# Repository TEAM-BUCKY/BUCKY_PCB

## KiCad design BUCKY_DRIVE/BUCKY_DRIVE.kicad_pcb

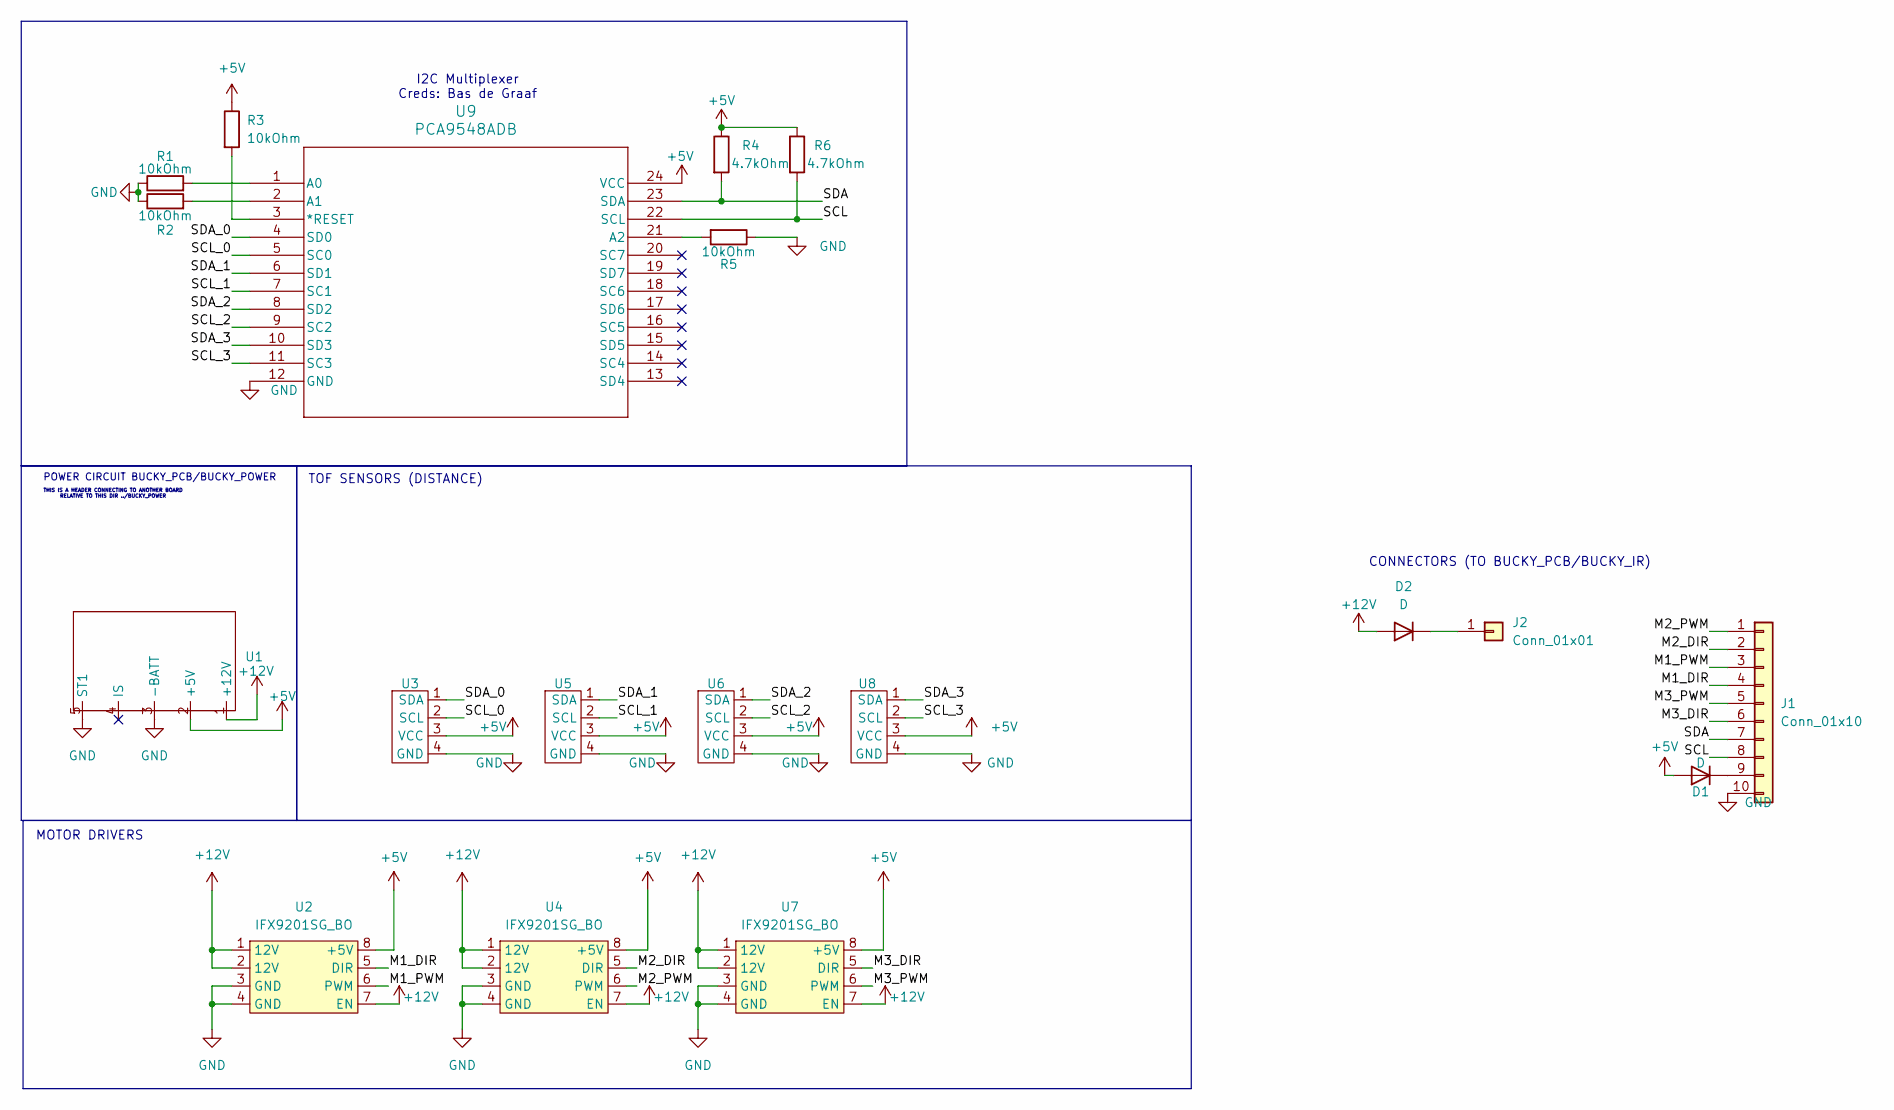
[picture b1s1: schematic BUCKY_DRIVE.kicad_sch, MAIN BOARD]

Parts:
D1: D; D_0805_2012Metric
D2: D
J1: Conn_01x10; CONN10_S10B-PH_JST
J2: Conn_01x01; PinHeader_1x01_P2.54mm_Vertical
R1, R2, R3, R5: 10kOhm; R_0805_2012Metric
R4, R6: 4.7kOhm; R_0805_2012Metric
U1: BUCKY_POWER
U2, U4, U7: IFX9201SG_BO
U3, U5, U6, U8: BUCKY_TOF
U9: PCA9548ADB; DB24

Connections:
+5V: D1.2 (A), J2.4, R3.1, R4.1, R6.1, U1.2 (+5V), U2.8 (+5V), U3.3 (VCC), U4.8 (+5V), U5.3 (VCC), U6.3 (VCC), U7.8 (+5V), U8.3 (VCC), U9.24 (VCC)
+12V: D2.2 (A), U1.1 (+12V), U2.1 (12V), U2.2 (12V), U2.7 (EN), U4.1 (12V), U4.2 (12V), U4.7 (EN), U7.1 (12V), U7.2 (12V), U7.7 (EN)
/M1_DIR: J1.4, U2.5 (DIR)
/M1_PWM: J1.3, U2.6 (PWM)
/M2_DIR: J1.2, U4.5 (DIR)
/M2_PWM: J1.1, U4.6 (PWM)
/M3_DIR: J1.6, U7.5 (DIR)
/M3_PWM: J1.5, U7.6 (PWM)
/SCL: J1.8, J2.2, R6.2, U9.22 (SCL)
/SCL_0: U3.2 (SCL), U9.5 (SC0)
/SCL_1: U5.2 (SCL), U9.7 (SC1)
/SCL_2: U6.2 (SCL), U9.9 (SC2)
/SCL_3: U8.2 (SCL), U9.11 (SC3)
/SDA: J1.7, J2.3, R4.2, U9.23 (SDA)
/SDA_0: U3.1 (SDA), U9.4 (SD0)
/SDA_1: U5.1 (SDA), U9.6 (SD1)
/SDA_2: U6.1 (SDA), U9.8 (SD2)
/SDA_3: U8.1 (SDA), U9.10 (SD3)
GND: D2.1 (K), J1.10, J2.1, R1.1, R2.1, R5.1, U1.3 (-BATT), U1.5 (ST1), U2.3 (GND), U2.4 (GND), U3.4 (GND), U4.3 (GND), U4.4 (GND), U5.4 (GND), U6.4 (GND), U7.3 (GND), U7.4 (GND), U8.4 (GND), U9.12 (GND)
unnamed: D1.1 (K), J1.9
unnamed: R3.2, U9.3 (*RESET)
unnamed: R1.2, U9.1 (A0)
unnamed: R2.2, U9.2 (A1)
unnamed: R5.2, U9.21 (A2)

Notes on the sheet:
CONNECTORS (TO BUCKY_PCB/BUCKY_IR)
TOF SENSORS (DISTANCE)
I2C Multiplexer Creds: Bas de Graaf
THIS IS A HEADER CONNECTING TO ANOTHER BOARD RELATIVE TO THIS DIR ../BUCKY_POWER
MOTOR DRIVERS
POWER CIRCUIT BUCKY_PCB/BUCKY_POWER

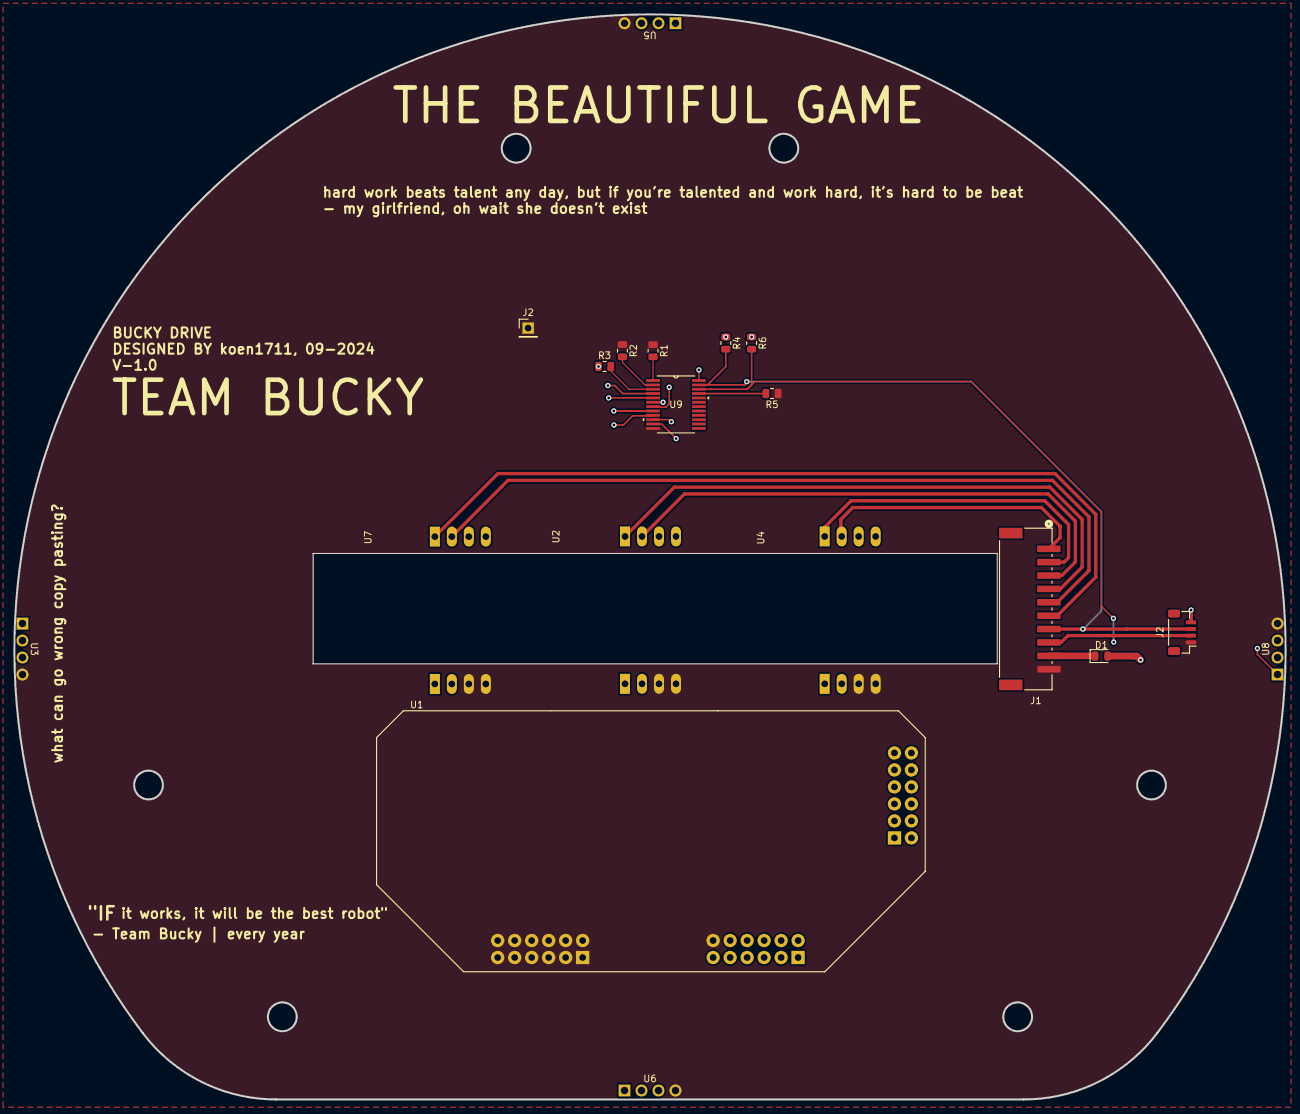
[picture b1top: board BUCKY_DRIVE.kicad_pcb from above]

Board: 4 copper layers, 190.0 x 162.2 mm, 19 parts (0 on the bottom side), 24 nets.

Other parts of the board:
J2#2: Conn_01x01; PinHeader_1x01_P2.54mm_Vertical

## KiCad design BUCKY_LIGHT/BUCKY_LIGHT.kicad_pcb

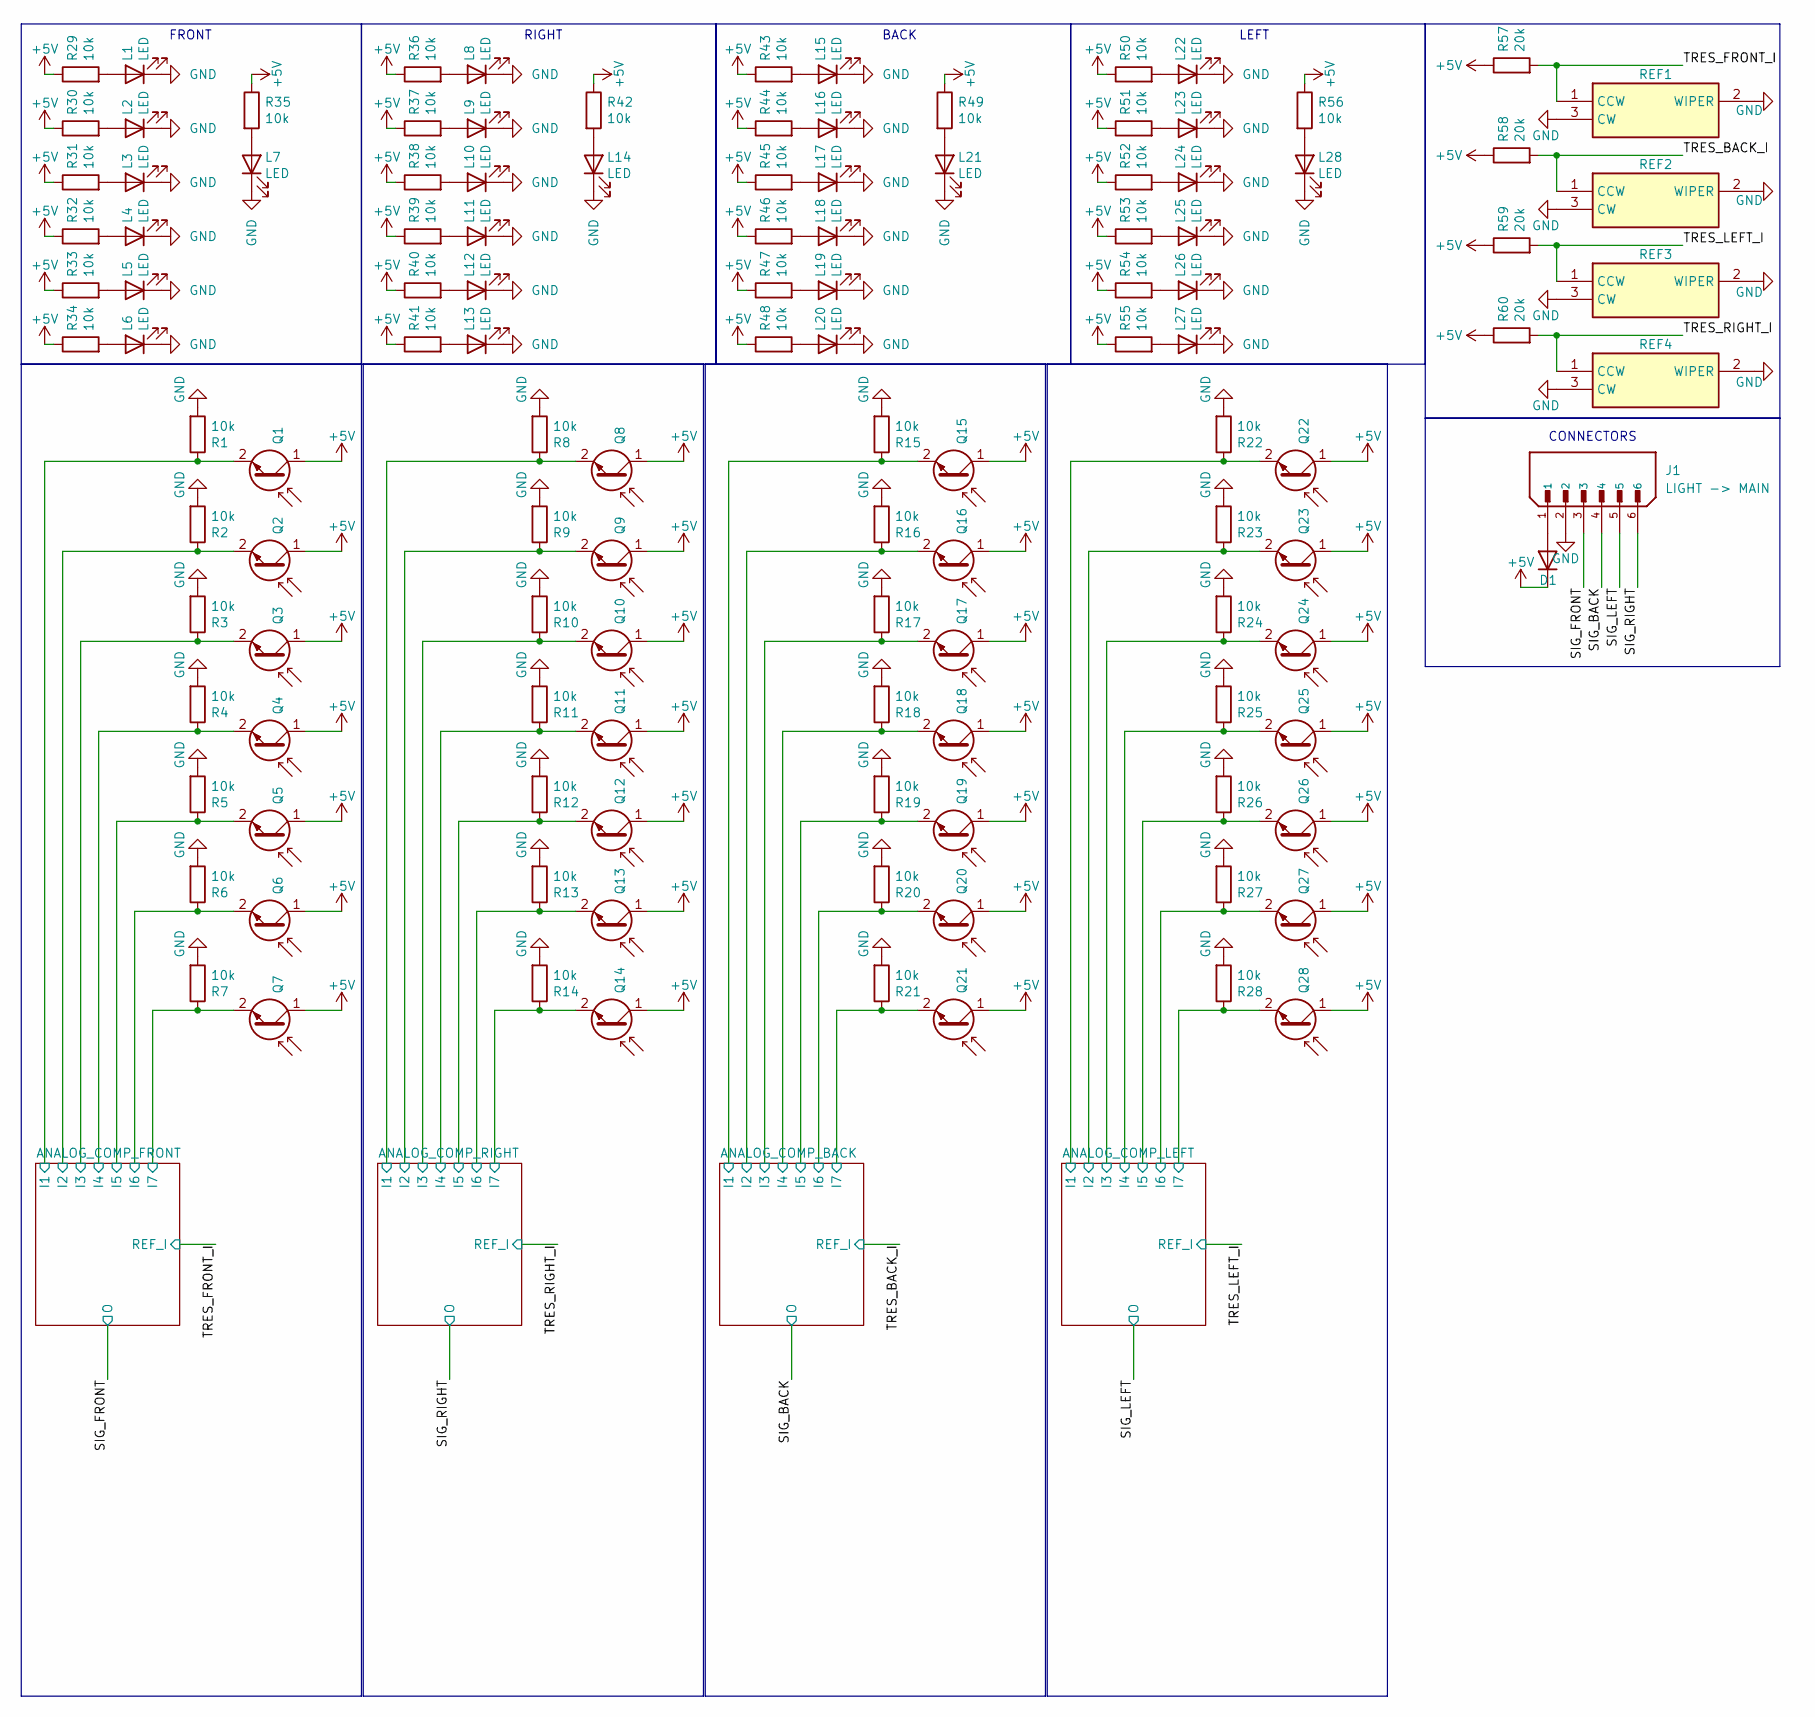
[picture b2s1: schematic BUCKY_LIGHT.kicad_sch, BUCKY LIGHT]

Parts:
D1: D; LED_PLCC-2_3.4x3.0mm_AK
J1: LIGHT -> MAIN; LIGHT_CONN; PARTREV 7/4/21
L1, L2, L3, L4, L5, L6, L7, L8, L9, L10, L11, L12, L13, L14, L15, L16, L17, L18, L19, L20, L21, L22, L23, L24, L25, L26, L27, L28: LED; LED_PLCC-2_3.4x3.0mm_AK
Q1, Q2, Q3, Q4, Q5, Q6, Q7, Q8, Q9, Q10, Q11, Q12, Q13, Q14, Q15, Q16, Q17, Q18, Q19, Q20, Q21, Q22, Q23, Q24, Q25, Q26, Q27, Q28: Q_Photo_NPN; XDCR_ALS-PT19-315C_L177_TR8
R1, R2, R3, R4, R5, R6, R7, R8, R9, R10, R11, R12, R13, R14, R15, R16, R17, R18, R19, R20, R21, R22, R23, R24, R25, R26, R27, R28, R29, R30, R31, R32, R33, R34, R35, R36, R37, R38, R39, R40, R41, R42, R43, R44, R45, R46, R47, R48, R49, R50, R51, R52, R53, R54, R55, R56: 10k; R_0805_2012Metric
R57, R58, R59, R60: 20k; R_0805_2012Metric
REF1, REF2, REF3, REF4: 3362P-1-103; VAR_RESISTOR; Mouser Part Number 652-3362P-1-103

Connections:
+5V: D1.1 (K), Q1.1 (C), Q2.1 (C), Q3.1 (C), Q4.1 (C), Q5.1 (C), Q6.1 (C), Q7.1 (C), Q8.1 (C), Q9.1 (C), Q10.1 (C), Q11.1 (C), Q12.1 (C), Q13.1 (C), Q14.1 (C), Q15.1 (C), Q16.1 (C), Q17.1 (C), Q18.1 (C), Q19.1 (C), Q20.1 (C), Q21.1 (C), Q22.1 (C), Q23.1 (C), Q24.1 (C), Q25.1 (C), Q26.1 (C), Q27.1 (C), Q28.1 (C), R29.1, R30.1, R31.1, R32.1, R33.1, R34.1, R35.1, R36.1, R37.1, R38.1, R39.1, R40.1, R41.1, R42.1, R43.1, R44.1, R45.1, R46.1, R47.1, R48.1, R49.1, R50.1, R51.1, R52.1, R53.1, R54.1, R55.1, R56.1, R57.1, R58.1, R59.1, R60.1; also elsewhere on the board
/ANALOG_COMP_BACK/I1: Q15.2 (E), R15.1; also elsewhere on the board
/ANALOG_COMP_BACK/I2: Q16.2 (E), R16.1; also elsewhere on the board
/ANALOG_COMP_BACK/I3: Q17.2 (E), R17.1; also elsewhere on the board
/ANALOG_COMP_BACK/I4: Q18.2 (E), R18.1; also elsewhere on the board
/ANALOG_COMP_BACK/I5: Q19.2 (E), R19.1; also elsewhere on the board
/ANALOG_COMP_BACK/I6: Q20.2 (E), R20.1; also elsewhere on the board
/ANALOG_COMP_BACK/I7: Q21.2 (E), R21.1; also elsewhere on the board
/ANALOG_COMP_FRONT/I1: Q1.2 (E), R1.1; also elsewhere on the board
/ANALOG_COMP_FRONT/I2: Q2.2 (E), R2.1; also elsewhere on the board
/ANALOG_COMP_FRONT/I3: Q3.2 (E), R3.1; also elsewhere on the board
/ANALOG_COMP_FRONT/I4: Q4.2 (E), R4.1; also elsewhere on the board
/ANALOG_COMP_FRONT/I5: Q5.2 (E), R5.1; also elsewhere on the board
/ANALOG_COMP_FRONT/I6: Q6.2 (E), R6.1; also elsewhere on the board
/ANALOG_COMP_FRONT/I7: Q7.2 (E), R7.1; also elsewhere on the board
/ANALOG_COMP_LEFT/I1: Q22.2 (E), R22.1; also elsewhere on the board
/ANALOG_COMP_LEFT/I2: Q23.2 (E), R23.1; also elsewhere on the board
/ANALOG_COMP_LEFT/I3: Q24.2 (E), R24.1; also elsewhere on the board
/ANALOG_COMP_LEFT/I4: Q25.2 (E), R25.1; also elsewhere on the board
/ANALOG_COMP_LEFT/I5: Q26.2 (E), R26.1; also elsewhere on the board
/ANALOG_COMP_LEFT/I6: Q27.2 (E), R27.1; also elsewhere on the board
/ANALOG_COMP_LEFT/I7: Q28.2 (E), R28.1; also elsewhere on the board
/ANALOG_COMP_RIGHT/I1: Q8.2 (E), R8.1; also elsewhere on the board
/ANALOG_COMP_RIGHT/I2: Q9.2 (E), R9.1; also elsewhere on the board
/ANALOG_COMP_RIGHT/I3: Q10.2 (E), R10.1; also elsewhere on the board
/ANALOG_COMP_RIGHT/I4: Q11.2 (E), R11.1; also elsewhere on the board
/ANALOG_COMP_RIGHT/I5: Q12.2 (E), R12.1; also elsewhere on the board
/ANALOG_COMP_RIGHT/I6: Q13.2 (E), R13.1; also elsewhere on the board
/ANALOG_COMP_RIGHT/I7: Q14.2 (E), R14.1; also elsewhere on the board
/SIG_BACK: J1.4; also elsewhere on the board
/SIG_FRONT: J1.3; also elsewhere on the board
/SIG_LEFT: J1.5; also elsewhere on the board
/SIG_RIGHT: J1.6; also elsewhere on the board
/TRES_BACK_I: R58.2, REF2.1 (CCW); also elsewhere on the board
/TRES_FRONT_I: R57.2, REF1.1 (CCW); also elsewhere on the board
/TRES_LEFT_I: R59.2, REF3.1 (CCW); also elsewhere on the board
/TRES_RIGHT_I: R60.2, REF4.1 (CCW); also elsewhere on the board
GND: J1.2, L1.1 (K), L2.1 (K), L3.1 (K), L4.1 (K), L5.1 (K), L6.1 (K), L7.1 (K), L8.1 (K), L9.1 (K), L10.1 (K), L11.1 (K), L12.1 (K), L13.1 (K), L14.1 (K), L15.1 (K), L16.1 (K), L17.1 (K), L18.1 (K), L19.1 (K), L20.1 (K), L21.1 (K), L22.1 (K), L23.1 (K), L24.1 (K), L25.1 (K), L26.1 (K), L27.1 (K), L28.1 (K), R1.2, R2.2, R3.2, R4.2, R5.2, R6.2, R7.2, R8.2, R9.2, R10.2, R11.2, R12.2, R13.2, R14.2, R15.2, R16.2, R17.2, R18.2, R19.2, R20.2, R21.2, R22.2, R23.2, R24.2, R25.2, R26.2, R27.2, R28.2, REF1.2 (WIPER), REF1.3 (CW), REF2.2 (WIPER), REF2.3 (CW), REF3.2 (WIPER), REF3.3 (CW), REF4.2 (WIPER), REF4.3 (CW); also elsewhere on the board
unnamed: D1.2 (A), J1.1
unnamed: L1.2 (A), R29.2
unnamed: L2.2 (A), R30.2
unnamed: L3.2 (A), R31.2
unnamed: L4.2 (A), R32.2
unnamed: L5.2 (A), R33.2
unnamed: L6.2 (A), R34.2
unnamed: L7.2 (A), R35.2
unnamed: L8.2 (A), R36.2
unnamed: L9.2 (A), R37.2
unnamed: L10.2 (A), R38.2
unnamed: L11.2 (A), R39.2
unnamed: L12.2 (A), R40.2
unnamed: L13.2 (A), R41.2
unnamed: L14.2 (A), R42.2
unnamed: L15.2 (A), R43.2
unnamed: L16.2 (A), R44.2
unnamed: L17.2 (A), R45.2
unnamed: L18.2 (A), R46.2
unnamed: L19.2 (A), R47.2
unnamed: L20.2 (A), R48.2
unnamed: L21.2 (A), R49.2
unnamed: L22.2 (A), R50.2
unnamed: L23.2 (A), R51.2
unnamed: L24.2 (A), R52.2
unnamed: L25.2 (A), R53.2
unnamed: L26.2 (A), R54.2
unnamed: L27.2 (A), R55.2
unnamed: L28.2 (A), R56.2

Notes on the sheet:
LEFT
CONNECTORS
FRONT
BACK
RIGHT

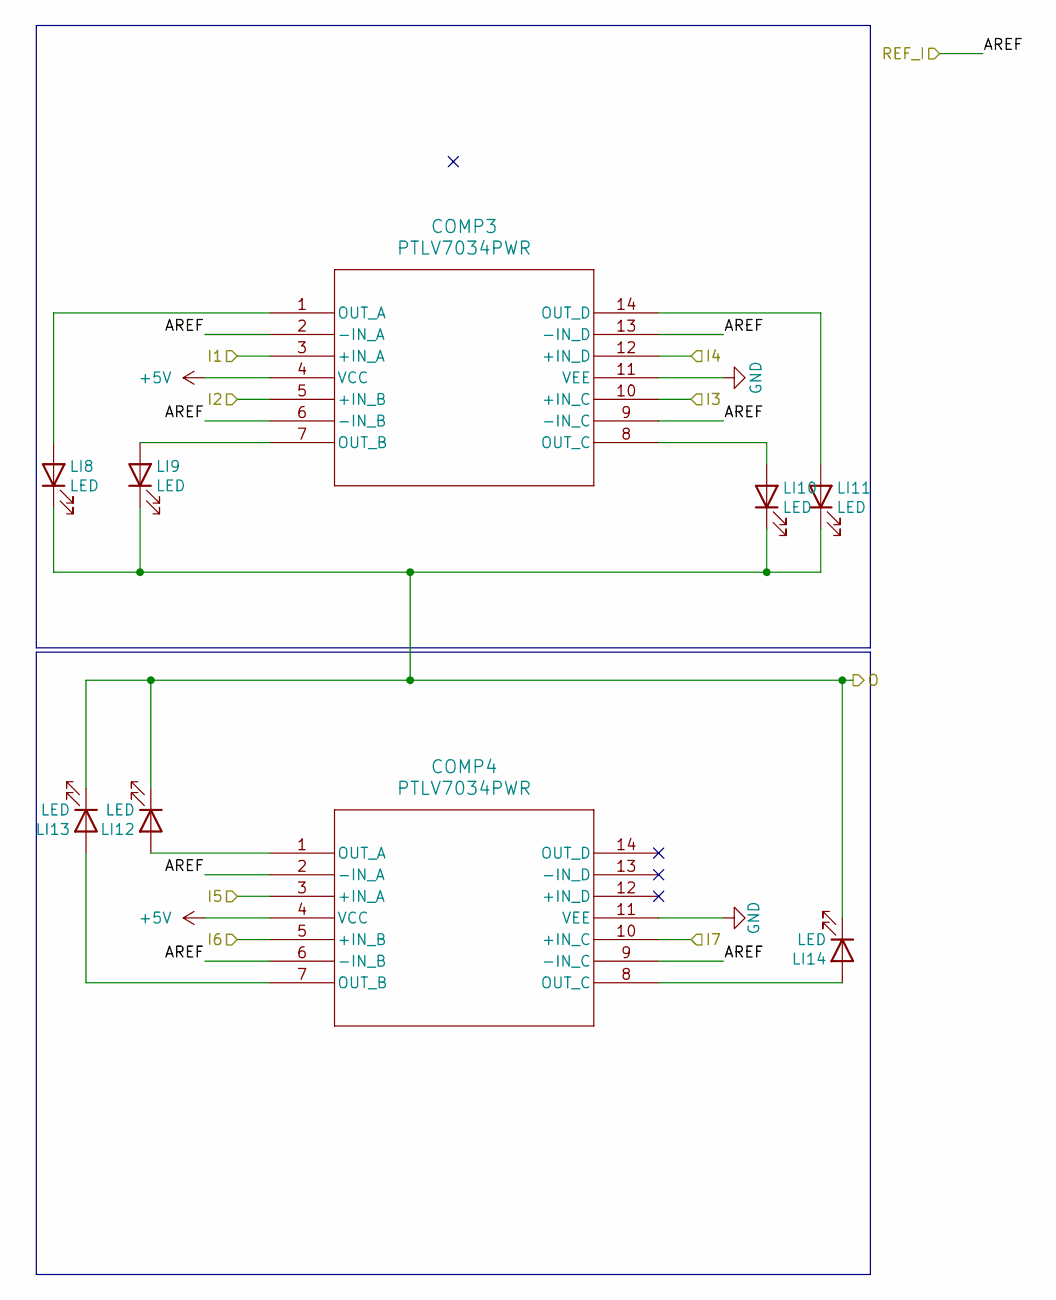
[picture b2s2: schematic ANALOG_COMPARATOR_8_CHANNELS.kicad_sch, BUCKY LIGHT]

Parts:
COMP3, COMP4: PTLV7034PWR; ANALOG_COMP
LI8, LI9, LI10, LI11, LI12, LI13, LI14: LED; LED_0805_2012Metric

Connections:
+5V: COMP3.4 (VCC), COMP4.4 (VCC); also elsewhere on the board
/ANALOG_COMP_RIGHT/I1: COMP3.3 (+IN_A); also elsewhere on the board
/ANALOG_COMP_RIGHT/I2: COMP3.5 (+IN_B); also elsewhere on the board
/ANALOG_COMP_RIGHT/I3: COMP3.10 (+IN_C); also elsewhere on the board
/ANALOG_COMP_RIGHT/I4: COMP3.12 (+IN_D); also elsewhere on the board
/ANALOG_COMP_RIGHT/I5: COMP4.3 (+IN_A); also elsewhere on the board
/ANALOG_COMP_RIGHT/I6: COMP4.5 (+IN_B); also elsewhere on the board
/ANALOG_COMP_RIGHT/I7: COMP4.10 (+IN_C); also elsewhere on the board
/SIG_RIGHT: LI8.1 (K), LI9.1 (K), LI10.1 (K), LI11.1 (K), LI12.1 (K), LI13.1 (K), LI14.1 (K); also elsewhere on the board
/TRES_RIGHT_I: COMP3.2 (-IN_A), COMP3.6 (-IN_B), COMP3.9 (-IN_C), COMP3.13 (-IN_D), COMP4.2 (-IN_A), COMP4.6 (-IN_B), COMP4.9 (-IN_C); also elsewhere on the board
GND: COMP3.11 (VEE), COMP4.11 (VEE); also elsewhere on the board
unnamed: COMP3.1 (OUT_A), LI8.2 (A)
unnamed: COMP3.7 (OUT_B), LI9.2 (A)
unnamed: COMP3.8 (OUT_C), LI10.2 (A)
unnamed: COMP3.14 (OUT_D), LI11.2 (A)
unnamed: COMP4.1 (OUT_A), LI12.2 (A)
unnamed: COMP4.7 (OUT_B), LI13.2 (A)
unnamed: COMP4.8 (OUT_C), LI14.2 (A)

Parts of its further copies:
COMP1, COMP2, COMP5, COMP6, COMP7, COMP8: PTLV7034PWR; ANALOG_COMP
LI1, LI2, LI3, LI4, LI5, LI6, LI7, LI15, LI16, LI17, LI18, LI19, LI20, LI21, LI22, LI23, LI24, LI25, LI26, LI27, LI28: LED; LED_0805_2012Metric

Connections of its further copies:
+5V: COMP1.4 (VCC), COMP2.4 (VCC), COMP5.4 (VCC), COMP6.4 (VCC), COMP7.4 (VCC), COMP8.4 (VCC); also elsewhere on the board
/ANALOG_COMP_BACK/I1: COMP5.3 (+IN_A); also elsewhere on the board
/ANALOG_COMP_BACK/I2: COMP5.5 (+IN_B); also elsewhere on the board
/ANALOG_COMP_BACK/I3: COMP5.10 (+IN_C); also elsewhere on the board
/ANALOG_COMP_BACK/I4: COMP5.12 (+IN_D); also elsewhere on the board
/ANALOG_COMP_BACK/I5: COMP6.3 (+IN_A); also elsewhere on the board
/ANALOG_COMP_BACK/I6: COMP6.5 (+IN_B); also elsewhere on the board
/ANALOG_COMP_BACK/I7: COMP6.10 (+IN_C); also elsewhere on the board
/ANALOG_COMP_FRONT/I1: COMP1.3 (+IN_A); also elsewhere on the board
/ANALOG_COMP_FRONT/I2: COMP1.5 (+IN_B); also elsewhere on the board
/ANALOG_COMP_FRONT/I3: COMP1.10 (+IN_C); also elsewhere on the board
/ANALOG_COMP_FRONT/I4: COMP1.12 (+IN_D); also elsewhere on the board
/ANALOG_COMP_FRONT/I5: COMP2.3 (+IN_A); also elsewhere on the board
/ANALOG_COMP_FRONT/I6: COMP2.5 (+IN_B); also elsewhere on the board
/ANALOG_COMP_FRONT/I7: COMP2.10 (+IN_C); also elsewhere on the board
/ANALOG_COMP_LEFT/I1: COMP7.3 (+IN_A); also elsewhere on the board
/ANALOG_COMP_LEFT/I2: COMP7.5 (+IN_B); also elsewhere on the board
/ANALOG_COMP_LEFT/I3: COMP7.10 (+IN_C); also elsewhere on the board
/ANALOG_COMP_LEFT/I4: COMP7.12 (+IN_D); also elsewhere on the board
/ANALOG_COMP_LEFT/I5: COMP8.3 (+IN_A); also elsewhere on the board
/ANALOG_COMP_LEFT/I6: COMP8.5 (+IN_B); also elsewhere on the board
/ANALOG_COMP_LEFT/I7: COMP8.10 (+IN_C); also elsewhere on the board
/SIG_BACK: LI15.1 (K), LI16.1 (K), LI17.1 (K), LI18.1 (K), LI19.1 (K), LI20.1 (K), LI21.1 (K); also elsewhere on the board
/SIG_FRONT: LI1.1 (K), LI2.1 (K), LI3.1 (K), LI4.1 (K), LI5.1 (K), LI6.1 (K), LI7.1 (K); also elsewhere on the board
/SIG_LEFT: LI22.1 (K), LI23.1 (K), LI24.1 (K), LI25.1 (K), LI26.1 (K), LI27.1 (K), LI28.1 (K); also elsewhere on the board
/TRES_BACK_I: COMP5.2 (-IN_A), COMP5.6 (-IN_B), COMP5.9 (-IN_C), COMP5.13 (-IN_D), COMP6.2 (-IN_A), COMP6.6 (-IN_B), COMP6.9 (-IN_C); also elsewhere on the board
/TRES_FRONT_I: COMP1.2 (-IN_A), COMP1.6 (-IN_B), COMP1.9 (-IN_C), COMP1.13 (-IN_D), COMP2.2 (-IN_A), COMP2.6 (-IN_B), COMP2.9 (-IN_C); also elsewhere on the board
/TRES_LEFT_I: COMP7.2 (-IN_A), COMP7.6 (-IN_B), COMP7.9 (-IN_C), COMP7.13 (-IN_D), COMP8.2 (-IN_A), COMP8.6 (-IN_B), COMP8.9 (-IN_C); also elsewhere on the board
GND: COMP1.11 (VEE), COMP2.11 (VEE), COMP5.11 (VEE), COMP6.11 (VEE), COMP7.11 (VEE), COMP8.11 (VEE); also elsewhere on the board
unnamed: COMP1.1 (OUT_A), LI1.2 (A)
unnamed: COMP1.7 (OUT_B), LI2.2 (A)
unnamed: COMP1.8 (OUT_C), LI3.2 (A)
unnamed: COMP1.14 (OUT_D), LI4.2 (A)
unnamed: COMP2.1 (OUT_A), LI5.2 (A)
unnamed: COMP2.7 (OUT_B), LI6.2 (A)
unnamed: COMP2.8 (OUT_C), LI7.2 (A)
unnamed: COMP5.1 (OUT_A), LI15.2 (A)
unnamed: COMP5.7 (OUT_B), LI16.2 (A)
unnamed: COMP5.8 (OUT_C), LI17.2 (A)
unnamed: COMP5.14 (OUT_D), LI18.2 (A)
unnamed: COMP6.1 (OUT_A), LI19.2 (A)
unnamed: COMP6.7 (OUT_B), LI20.2 (A)
unnamed: COMP6.8 (OUT_C), LI21.2 (A)
unnamed: COMP7.1 (OUT_A), LI22.2 (A)
unnamed: COMP7.7 (OUT_B), LI23.2 (A)
unnamed: COMP7.8 (OUT_C), LI24.2 (A)
unnamed: COMP7.14 (OUT_D), LI25.2 (A)
unnamed: COMP8.1 (OUT_A), LI26.2 (A)
unnamed: COMP8.7 (OUT_B), LI27.2 (A)
unnamed: COMP8.8 (OUT_C), LI28.2 (A)

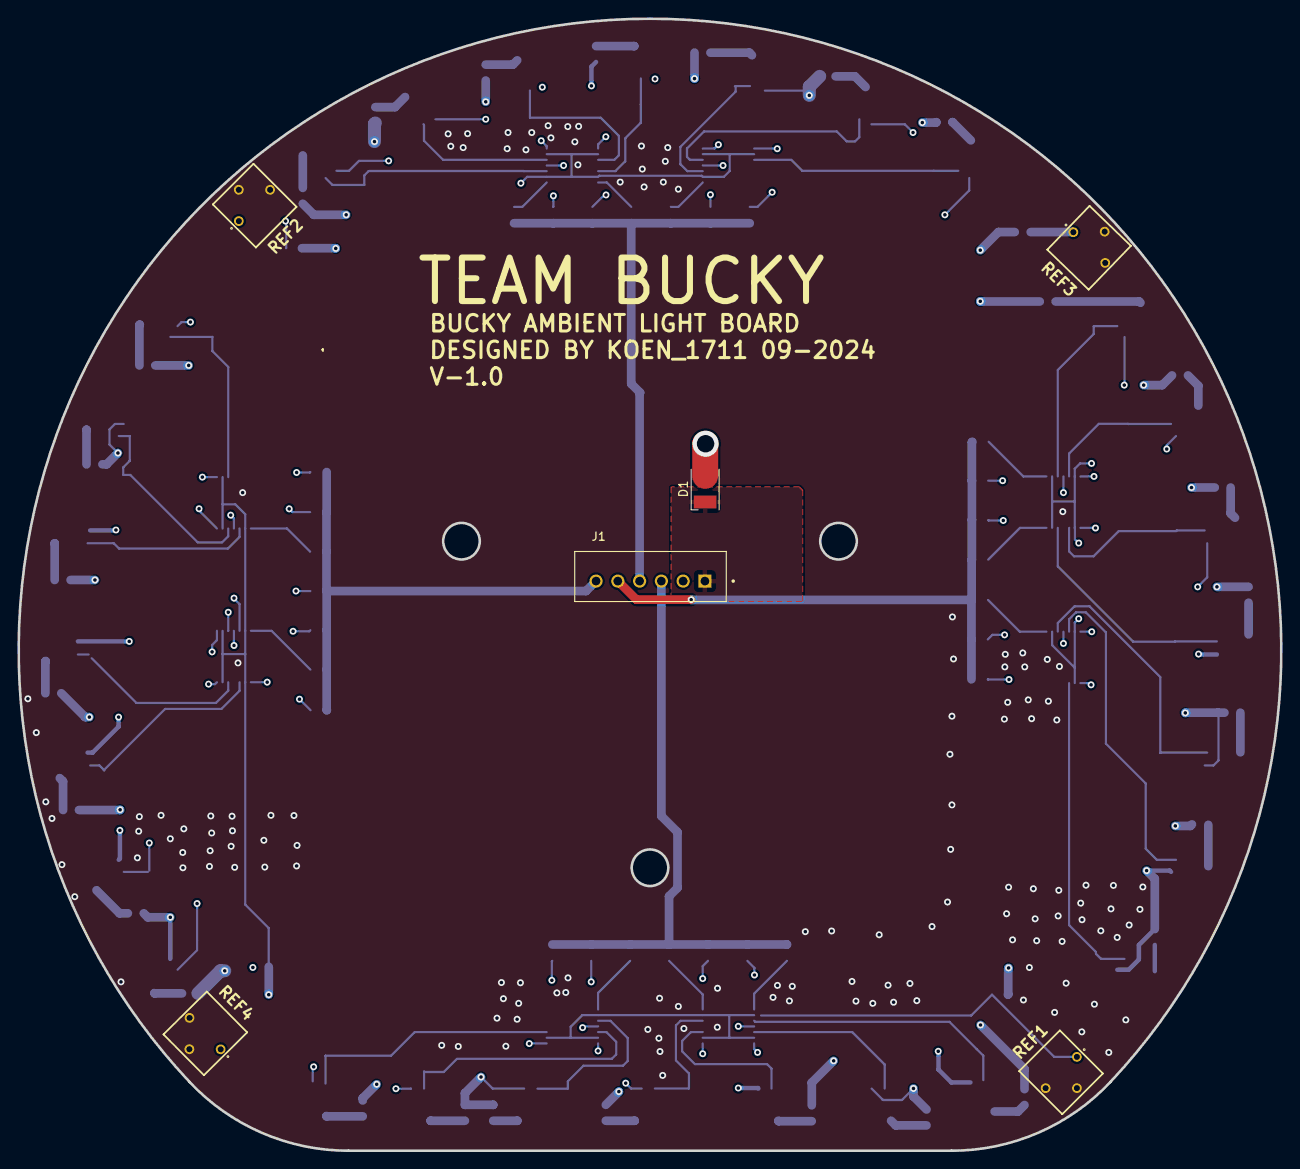
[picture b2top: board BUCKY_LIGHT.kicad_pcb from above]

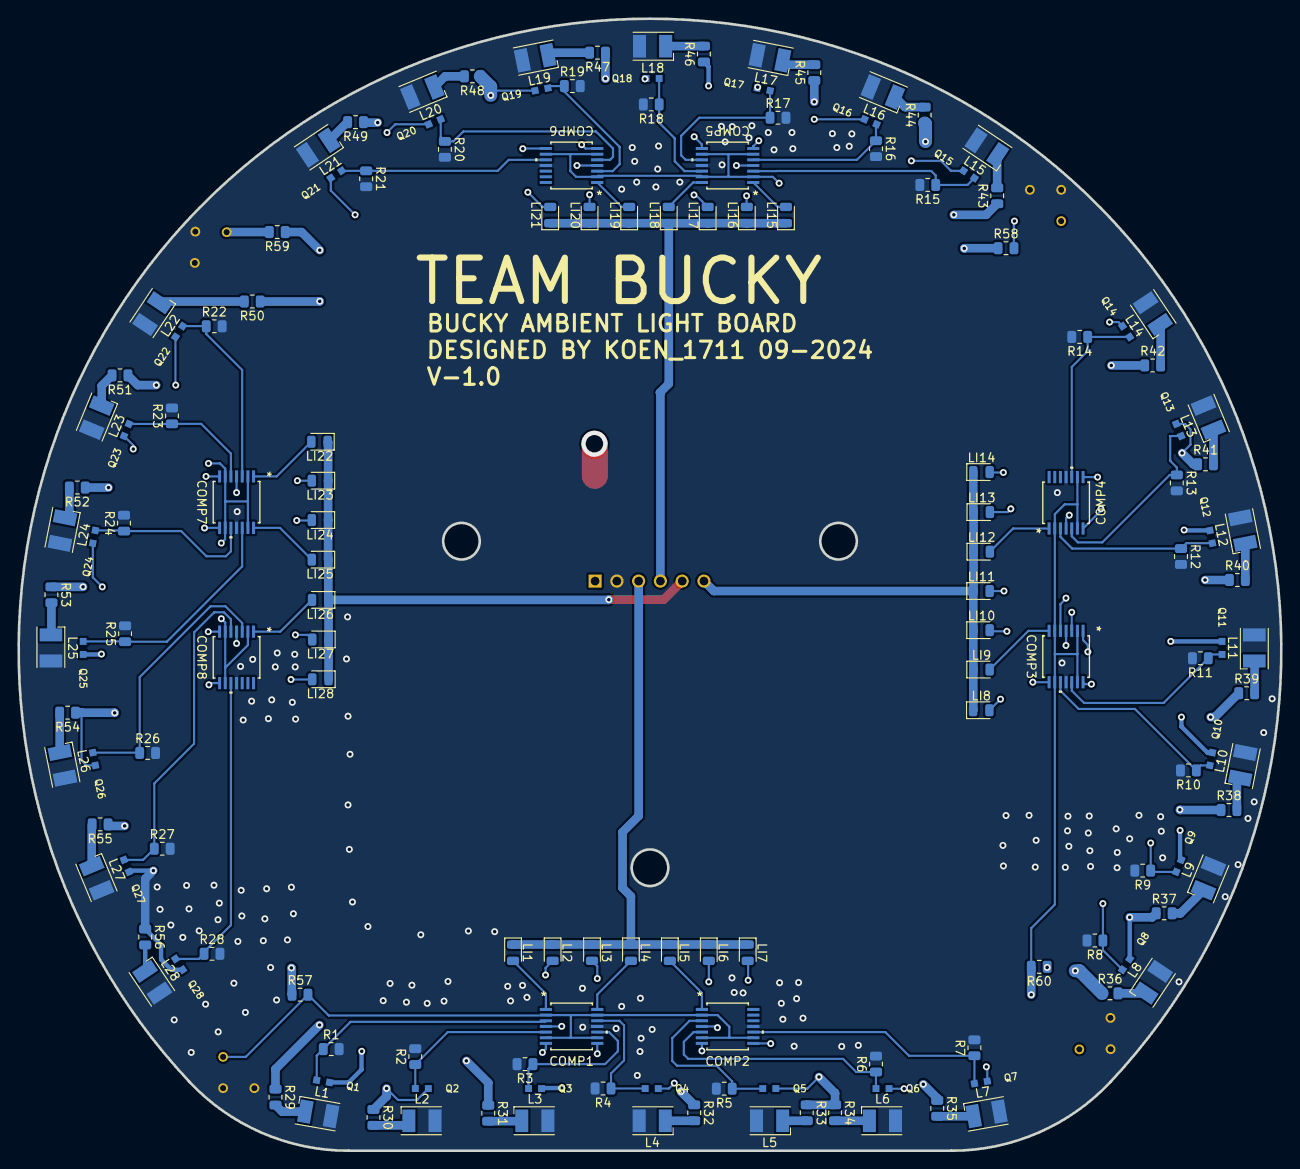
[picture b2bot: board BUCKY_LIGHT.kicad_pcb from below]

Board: 4 copper layers, 145.0 x 130.0 mm, 158 parts (152 on the bottom side), 95 nets.

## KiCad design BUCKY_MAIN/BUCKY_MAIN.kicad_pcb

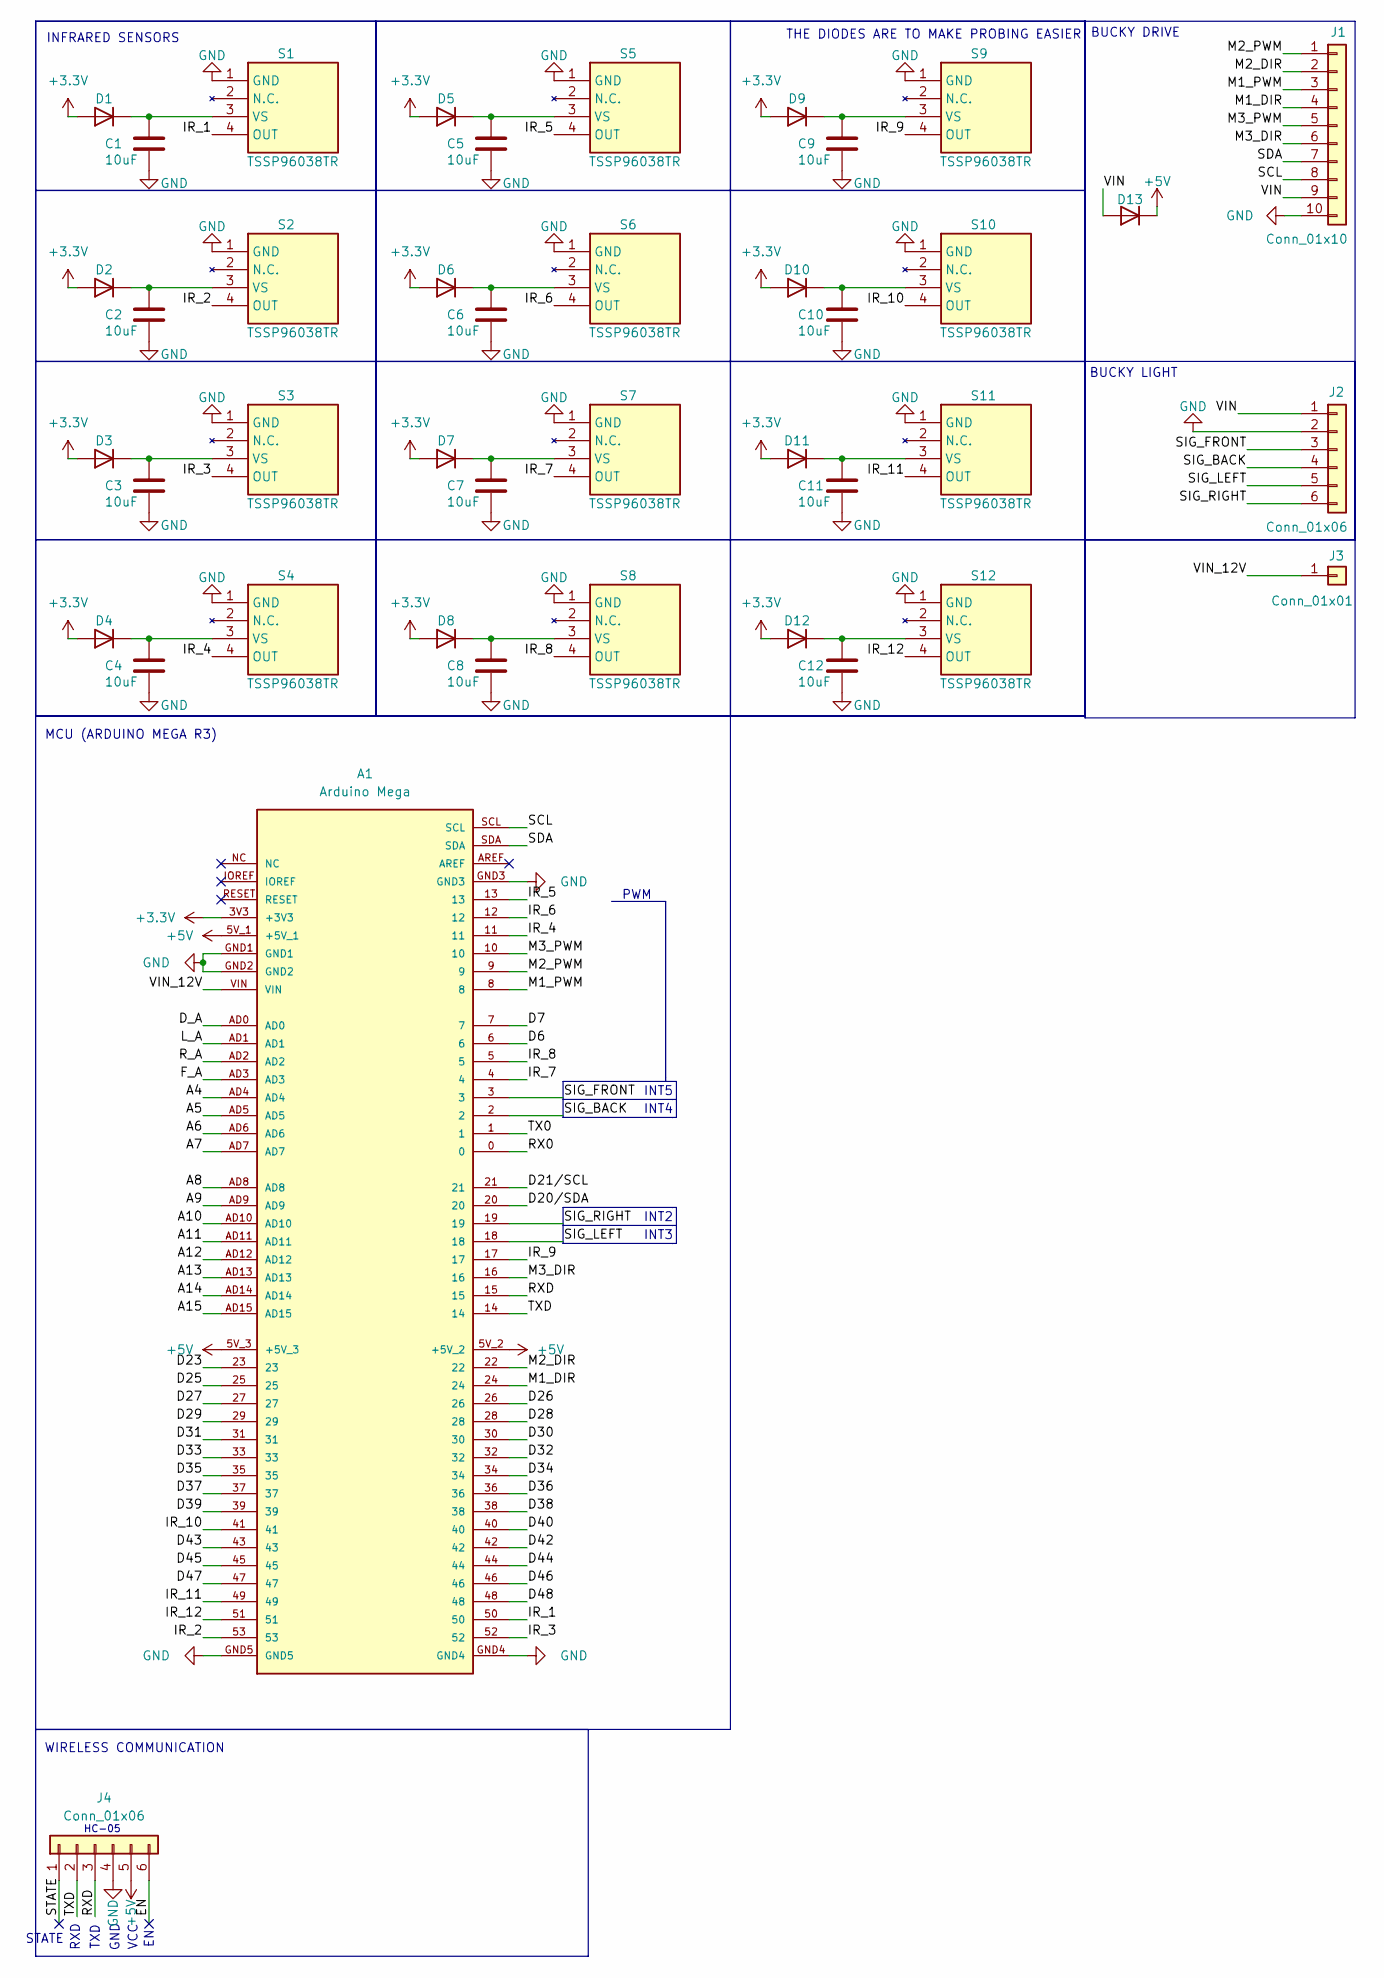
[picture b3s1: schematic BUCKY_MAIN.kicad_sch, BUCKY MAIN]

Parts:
A1: Arduino Mega; ARDUINO_MEGA
C1, C2, C3, C4, C5, C6, C7, C8, C9, C10, C11, C12: 10uF; C_0805_2012Metric
D1, D2, D3, D4, D5, D6, D7, D8, D9, D10, D11, D12: D; D_0805_2012Metric
D13: D; D_3220_8050Metric
J1: Conn_01x10; CONN10_S10B-PH_JST
J2: Conn_01x06; LIGHT_CONN
J3: Conn_01x01; PinHeader_1x01_P2.54mm_Vertical
J4: Conn_01x06; PinHeader_1x06_P2.54mm_Horizontal
S1, S2, S3, S4, S5, S6, S7, S8, S9, S10, S11, S12: TSSP96038TR; TSSP96038; Mouser Part Number 78-TSSP96038TR

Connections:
+3.3V: A1.3V3 (+3V3), D1.2 (A), D2.2 (A), D3.2 (A), D4.2 (A), D5.2 (A), D6.2 (A), D7.2 (A), D8.2 (A), D9.2 (A), D10.2 (A), D11.2 (A), D12.2 (A)
+5V: A1.5V_1 (+5V_1), A1.5V_2 (+5V_2), A1.5V_3 (+5V_3), D13.1 (K), J4.5
/A4: A1.AD4
/A5: A1.AD5
/A6: A1.AD6
/A7: A1.AD7
/A8: A1.AD8
/A9: A1.AD9
/A10: A1.AD10
/A11: A1.AD11
/A12: A1.AD12
/A13: A1.AD13
/A14: A1.AD14
/A15: A1.AD15
/D6: A1.6
/D7: A1.7
/D20/SDA: A1.20
/D21/SCL: A1.21
/D23: A1.23
/D25: A1.25
/D26: A1.26
/D27: A1.27
/D28: A1.28
/D29: A1.29
/D30: A1.30
/D31: A1.31
/D32: A1.32
/D33: A1.33
/D34: A1.34
/D35: A1.35
/D36: A1.36
/D37: A1.37
/D38: A1.38
/D39: A1.39
/D40: A1.40
/D42: A1.42
/D43: A1.43
/D44: A1.44
/D45: A1.45
/D46: A1.46
/D47: A1.47
/D48: A1.48
/D_A: A1.AD0
/EN: J4.6
/F_A: A1.AD3
/IR_1: A1.50, S1.4 (OUT)
/IR_2: A1.53, S2.4 (OUT)
/IR_3: A1.52, S3.4 (OUT)
/IR_4: A1.11, S4.4 (OUT)
/IR_5: A1.13, S5.4 (OUT)
/IR_6: A1.12, S6.4 (OUT)
/IR_7: A1.4, S7.4 (OUT)
/IR_8: A1.5, S8.4 (OUT)
/IR_9: A1.17, S9.4 (OUT)
/IR_10: A1.41, S10.4 (OUT)
/IR_11: A1.49, S11.4 (OUT)
/IR_12: A1.51, S12.4 (OUT)
/L_A: A1.AD1
/M1_DIR: A1.24, J1.4
/M1_PWM: A1.8, J1.3
/M2_DIR: A1.22, J1.2
/M2_PWM: A1.9, J1.1
/M3_DIR: A1.16, J1.6
/M3_PWM: A1.10, J1.5
/RX0: A1.0
/RXD: A1.15, J4.3
/R_A: A1.AD2
/SCL: A1.SCL, J1.8
/SDA: A1.SDA, J1.7
/SIG_BACK: A1.2, J2.4
/SIG_FRONT: A1.3, J2.3
/SIG_LEFT: A1.18, J2.5
/SIG_RIGHT: A1.19, J2.6
/STATE: J4.1
/TX0: A1.1
/TXD: A1.14, J4.2
/VIN: D13.2 (A), J1.9, J2.1
/VIN_12V: A1.VIN, J3.1
GND: A1.GND1, A1.GND2, A1.GND3, A1.GND4, A1.GND5, C1.1, C2.1, C3.1, C4.1, C5.1, C6.1, C7.1, C8.1, C9.1, C10.1, C11.1, C12.1, J1.10, J2.2, J4.4, S1.1 (GND), S2.1 (GND), S3.1 (GND), S4.1 (GND), S5.1 (GND), S6.1 (GND), S7.1 (GND), S8.1 (GND), S9.1 (GND), S10.1 (GND), S11.1 (GND), S12.1 (GND)
unnamed: C1.2, D1.1 (K), S1.3 (VS)
unnamed: C2.2, D2.1 (K), S2.3 (VS)
unnamed: C3.2, D3.1 (K), S3.3 (VS)
unnamed: C4.2, D4.1 (K), S4.3 (VS)
unnamed: C5.2, D5.1 (K), S5.3 (VS)
unnamed: C6.2, D6.1 (K), S6.3 (VS)
unnamed: C7.2, D7.1 (K), S7.3 (VS)
unnamed: C8.2, D8.1 (K), S8.3 (VS)
unnamed: C9.2, D9.1 (K), S9.3 (VS)
unnamed: C10.2, D10.1 (K), S10.3 (VS)
unnamed: C11.2, D11.1 (K), S11.3 (VS)
unnamed: C12.2, D12.1 (K), S12.3 (VS)

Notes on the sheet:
HC-05
INT4
INT2
VCC
TXD
INT5
WIRELESS COMMUNICATION
BUCKY LIGHT
STATE
THE DIODES ARE TO MAKE PROBING EASIER
BUCKY DRIVE
PWM
INT3
RXD
GND
INFRARED SENSORS
MCU (ARDUINO MEGA R3)
